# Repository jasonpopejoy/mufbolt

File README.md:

# mufbolt
buffered multiple design files and gerbers for eurorack

first eurorack design. this project was to help me learn kicad. 

circuit design is based off barton musical circuits buffered multiple but changed the footprint to smd.

https://github.com/jasonpopejoy/muffbolt/blob/main/muffbolt.jpg

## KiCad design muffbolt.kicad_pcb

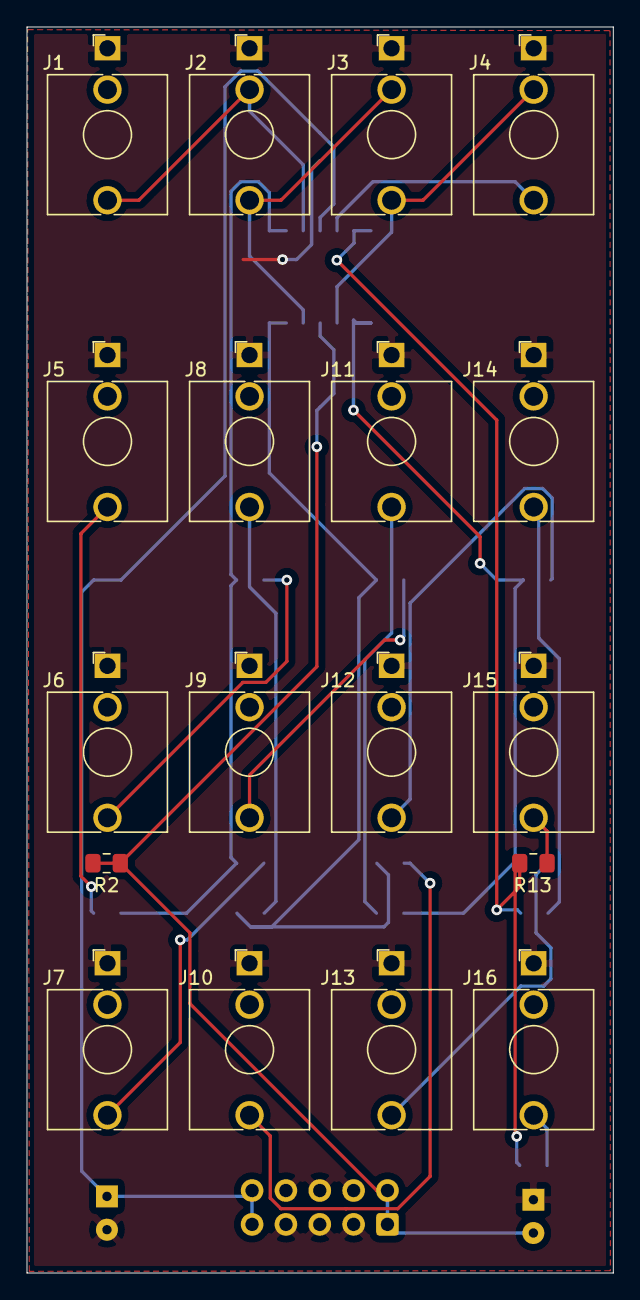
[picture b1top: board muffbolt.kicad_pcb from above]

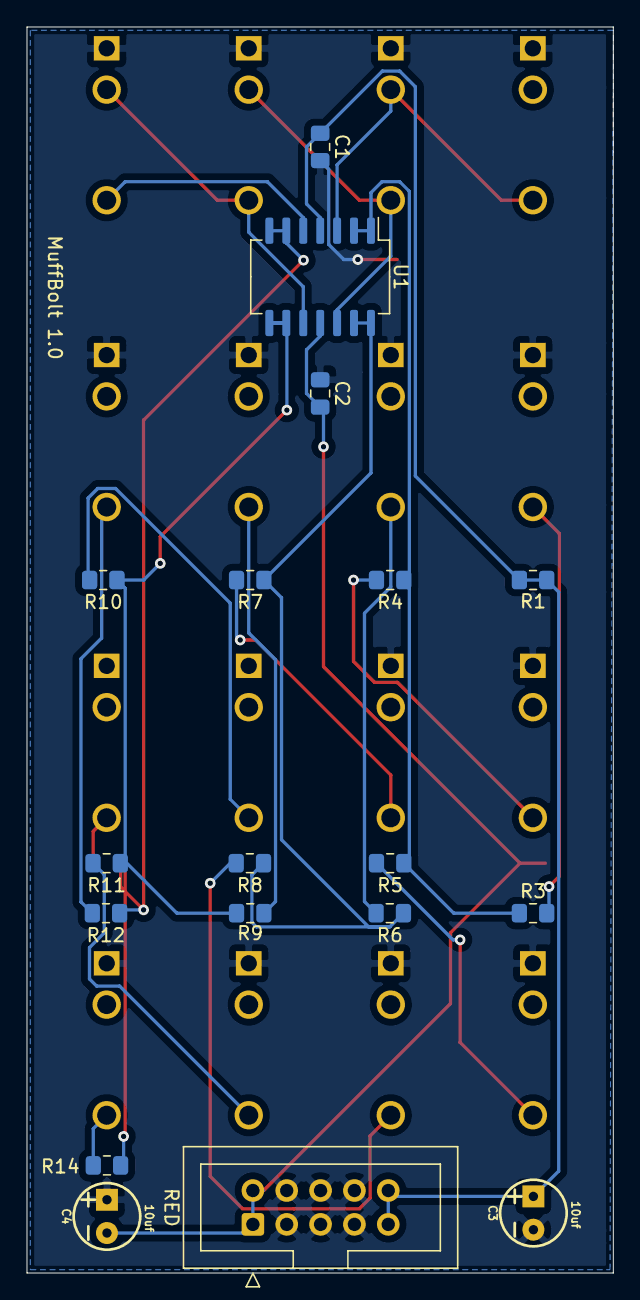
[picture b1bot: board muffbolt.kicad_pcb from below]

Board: 2 copper layers, 44.0 x 93.5 mm, 36 parts (18 on the bottom side), 23 nets.

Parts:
C1, C2: .1uf; C_0805_2012Metric_Pad1.15x1.40mm_HandSolder
C3, C4: 10uf; CPOL-RADIAL-2.5MM-5MM
J1: IN1; Jack_3.5mm_QingPu_WQP-PJ398SM_Vertical_CircularHoles
J2: IN2; Jack_3.5mm_QingPu_WQP-PJ398SM_Vertical_CircularHoles
J3: IN3; Jack_3.5mm_QingPu_WQP-PJ398SM_Vertical_CircularHoles
J4: IN4; Jack_3.5mm_QingPu_WQP-PJ398SM_Vertical_CircularHoles
J5, J8, J11, J14: OUT1; Jack_3.5mm_QingPu_WQP-PJ398SM_Vertical_CircularHoles
J6, J9, J12, J15: OUT2; Jack_3.5mm_QingPu_WQP-PJ398SM_Vertical_CircularHoles
J7, J10, J13, J16: OUT3; Jack_3.5mm_QingPu_WQP-PJ398SM_Vertical_CircularHoles
R1, R2: 10; R_0805_2012Metric_Pad1.15x1.40mm_HandSolder
R3, R4, R5, R6, R7, R8, R9, R10, R11, R12, R13, R14: 1K; R_0805_2012Metric_Pad1.15x1.40mm_HandSolder
RED: EURO_PWR_2x5; IDC-Header_2x05_P2.54mm_Vertical
U1: TL074; SO-14_5.3x10.2mm_P1.27mm

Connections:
+12V: C1.1, C3.1, R1.1, R1.2, RED.9, RED.10, U1.4
-12V: C2.2, C4.2, R2.1, R2.2, RED.1, RED.2, U1.11
GND: C1.2, C2.1, C3.2, C4.1, J1.S, J2.S, J3.S, J4.S, J5.S, J6.S, J7.S, J8.S, J9.S, J10.S, J11.S, J12.S, J13.S, J14.S, J15.S, J16.S, RED.3, RED.4, RED.5, RED.6, RED.7, RED.8
unnamed: J1.T, J2.TN, U1.3
unnamed: J2.T, J3.TN, U1.12
unnamed: J3.T, J4.TN, U1.10
unnamed: J4.T, U1.5
unnamed: J5.T, R3.2
unnamed: J6.T, R4.2
unnamed: J7.T, R5.2
unnamed: J8.T, R6.2
unnamed: J9.T, R7.2
unnamed: J10.T, R8.2
unnamed: J11.T, R9.2
unnamed: J12.T, R10.2
unnamed: J13.T, R11.2
unnamed: J14.T, R12.2
unnamed: J15.T, R13.2
unnamed: J16.T, R14.2
unnamed: R3.1, R4.1, R5.1, U1.1, U1.2
unnamed: R6.1, R7.1, R8.1, U1.13, U1.14
unnamed: R9.1, R10.1, R11.1, U1.8, U1.9
unnamed: R12.1, R13.1, R14.1, U1.6, U1.7

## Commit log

2023-03-10 bom deets
2023-03-10 kicad design file
2023-03-10 gerber files for pcb fab
